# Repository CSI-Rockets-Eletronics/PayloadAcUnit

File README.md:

# PayloadAcUnit
Electrical Design of the Payload AC Unit

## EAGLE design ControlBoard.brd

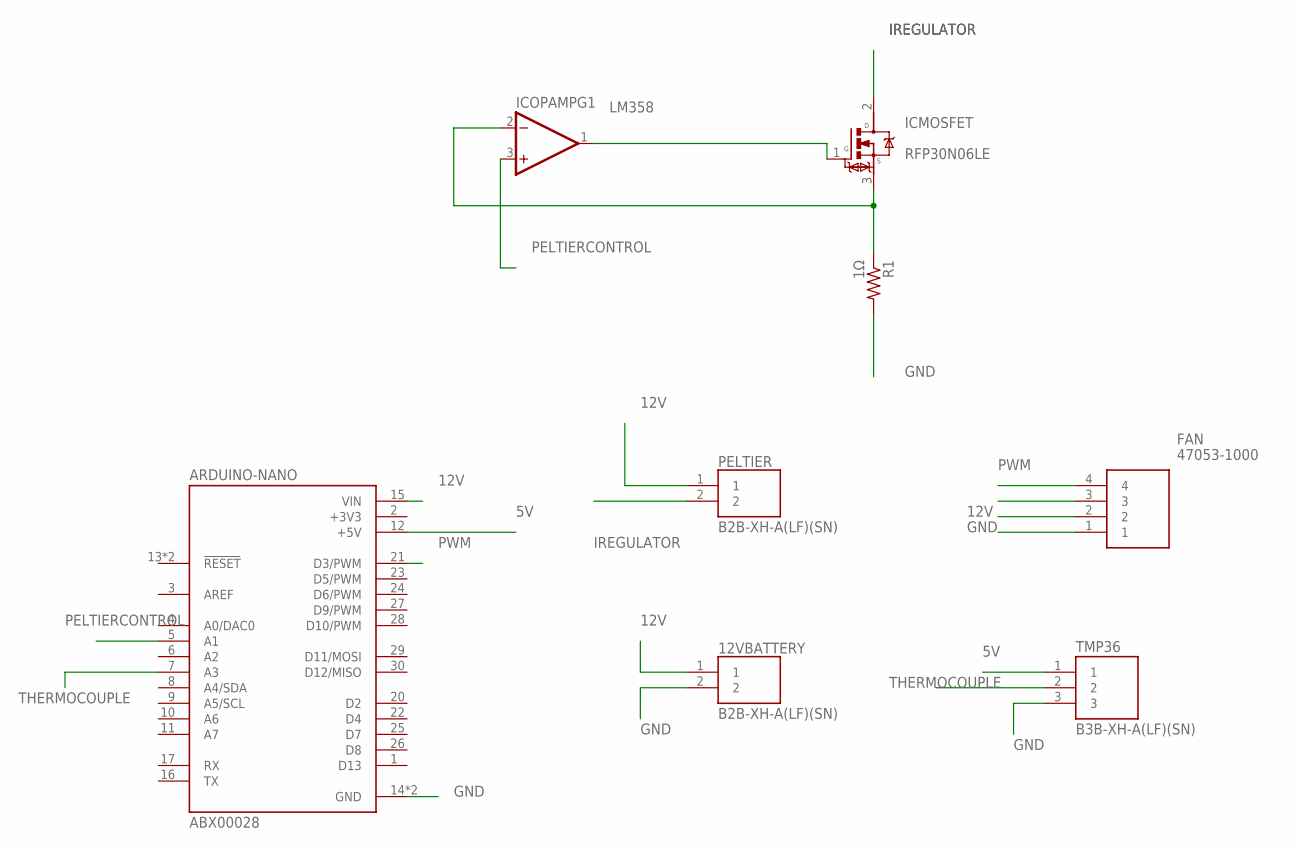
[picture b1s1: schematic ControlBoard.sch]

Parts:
12VBATTERY: B2B-XH-A(LF)(SN); JST_B2B-XH-A(LF)(SN)
ARDUINO-NANO: ABX00028; MODULE_ABX00028
FAN: 47053-1000; 470531000
ICMOSFET: RFP30N06LE; TRANS_RFP30N06LE
ICOPAMP: LM358; DIP08
PELTIER: B2B-XH-A(LF)(SN); JST_B2B-XH-A(LF)(SN)
R1: 1Ω; 0805-THM
TMP36: B3B-XH-A(LF)(SN); JST_B3B-XH-A(LF)(SN)

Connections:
5V: ARDUINO-NANO.12 (+5V), TMP36.1
12V: 12VBATTERY.1, ARDUINO-NANO.15 (VIN), FAN.2, PELTIER.1
+3V3: ARDUINO-NANO.2 (+3V3)
GND: 12VBATTERY.2, ARDUINO-NANO.14 (GND), ARDUINO-NANO.19 (GND), FAN.1, R1.2, TMP36.3
IREGULATOR: ICMOSFET.2 (D), PELTIER.2
unnamed: ICMOSFET.3 (S), ICOPAMP.2 (-IN), R1.1
unnamed: ICMOSFET.1 (G), ICOPAMP.1 (OUT)
PELTIERCONTROL: ARDUINO-NANO.5 (A1), ICOPAMP.3 (+IN)
PWM: ARDUINO-NANO.21 (D3/PWM), FAN.4
THERMOCOUPLE: ARDUINO-NANO.7 (A3), TMP36.2

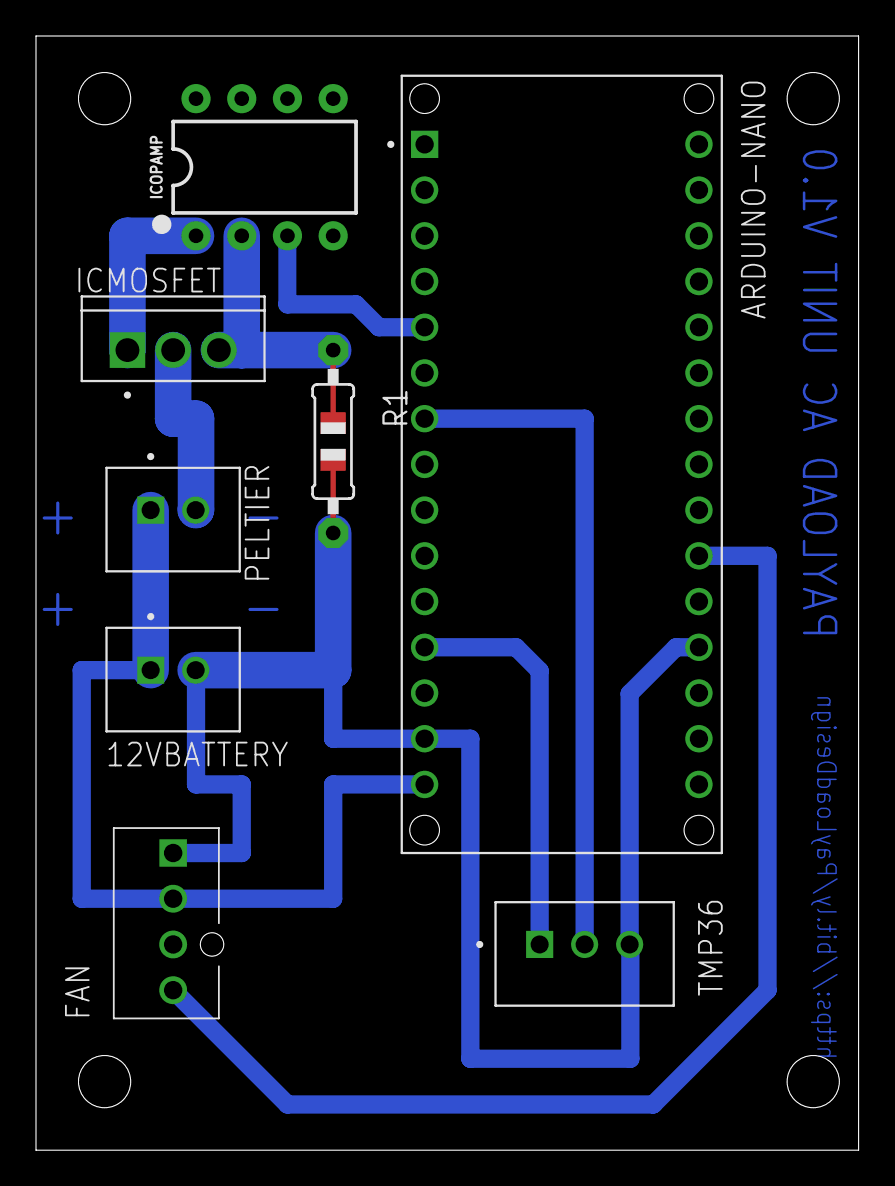
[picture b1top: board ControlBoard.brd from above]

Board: 2 copper layers, 45.7 x 61.9 mm, 8 parts (0 on the bottom side), 9 nets.

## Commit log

2022-02-10 Created a prototype of the control board using an arduino pro mini. Thinking about moving it to a Attiny85
2022-02-18 Made the first version of the pcb
2022-02-18 Cleaned a bit of the pcb and addded the tmp36 thermocouple
2022-03-07 Moved all traces to the bottom layer to allow for othermill pro manufacturing
2022-06-10 Made some images and created the code to control the payload
